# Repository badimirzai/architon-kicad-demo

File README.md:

# Architon KiCad BOM Demo

This repository is a minimal, reproducible demo of **Architon** scanning a **KiCad BOM CSV** and producing a deterministic JSON report.

What this demo proves (today):
- KiCad BOM CSV ingestion works
- A deterministic **DesignIR** JSON report is produced
- The workflow is automation-friendly (CI can run it)

What this demo does **not** claim (yet):
- Full schematic/netlist verification
- `rv scan .` project auto-discovery
- KiCad plugin integration

## Quickstart (local)

Prereqs:
- macOS / Linux
- Go installed (for `go install`), or install Architon via releases if you prefer

Install Architon CLI:

```bash
go install github.com/badimirzai/architon-cli@latest
```

Run scan:

```bash
rv scan bom/bom.csv --out .architon/architon-report.json
```

Inspect the report:

```bash
cat .architon/architon-report.json
```

## What’s in this repo

- `bom/bom.csv`  
  Exported from KiCad (Schematic Editor → Symbol Fields Table → Export CSV)

- `.architon/architon-report.json`  
  A reference report produced by running `rv scan` on the BOM

- `.github/workflows/architon.yml`  
  Runs `rv scan` on every push/PR

## Notes on “warnings”

If your BOM is missing optional/recommended fields (like Footprint for passives), Architon may emit parse warnings.
That’s fine for a demo, but if you want a “clean” demo output, assign footprints in KiCad before exporting the BOM.

## License

This demo repo is intended as an example project. Use any license you prefer for the repository itself.
Architon CLI is licensed separately in its own repository.

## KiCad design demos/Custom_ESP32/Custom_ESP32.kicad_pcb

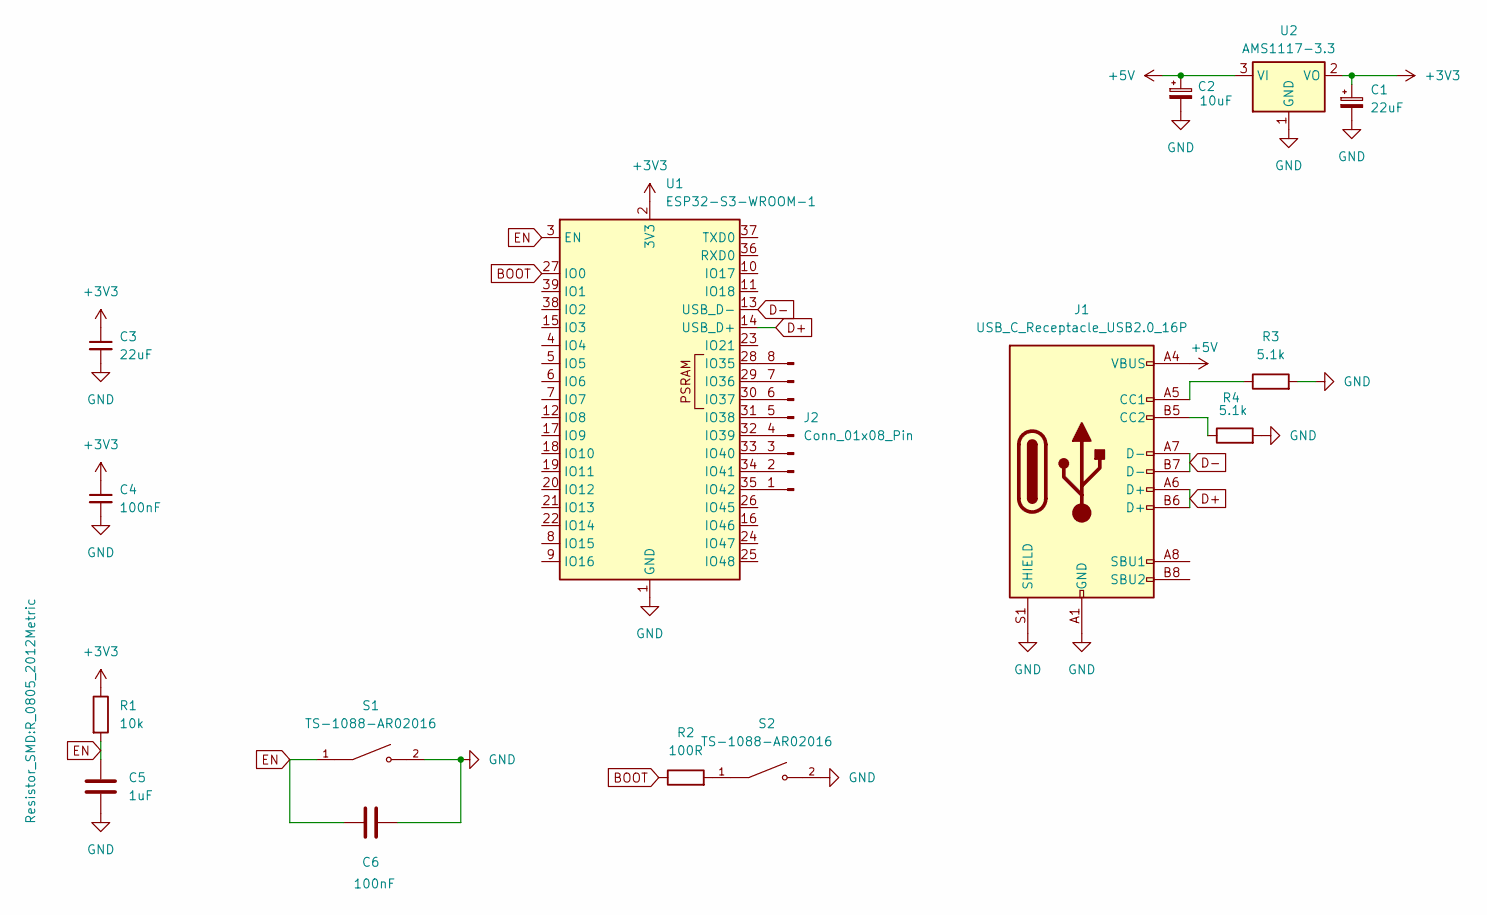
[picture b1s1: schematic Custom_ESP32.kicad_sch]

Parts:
C1: 22uF; CAPMP3216X180N
C2: 10uF; CAPMP3216X180N
C3: 22uF; 1uF_Unpolarized_CAPC2012X135N
C4, C6: 100nF; 1uF_Unpolarized_CAPC2012X135N
C5: 1uF; 1uF_Unpolarized_CAPC2012X135N
J1: USB_C_Receptacle_USB2.0_16P; GCT_USB4085-GF-A_REVA4
J2: Conn_01x08_Pin; PinHeader_1x08_P2.54mm_Vertical
R1: 10k; R_0805_2012Metric
R2: 100R; R_0805_2012Metric
R3, R4: 5.1k; R_0805_2012Metric
S1, S2: TS-1088-AR02016; SW_TS-1088-AR02016; PARTREV N/A
U1: ESP32-S3-WROOM-1
U2: AMS1117-3.3; SOT-223-3_TabPin2

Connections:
+3V3: C1.1, C3.1, C4.1, R1.1, U1.2 (3V3), U2.2 (VO)
+5V: C2.1, J1.A4 (VBUS), J1.A9 (VBUS), J1.B4 (VBUS), J1.B9 (VBUS), U2.3 (VI)
BOOT: R2.1, U1.27 (IO0)
D+: J1.A6 (D+), J1.B6 (D+), U1.14 (USB_D+)
D-: J1.A7 (D-), J1.B7 (D-), U1.13 (USB_D-)
EN: C5.1, C6.1, R1.2, S1.1, U1.3 (EN)
GND: C1.2, C2.2, C3.2, C4.2, C5.2, C6.2, J1.A1 (GND), J1.A12 (GND), J1.B1 (GND), J1.B12 (GND), J1.S1 (SHIELD), R3.2, R4.2, S1.2, S2.2, U1.1 (GND), U1.40 (GND), U1.41 (GND), U2.1 (GND)
unnamed: J1.A5 (CC1), R3.1
unnamed: J1.B5 (CC2), R4.1
unnamed: J2.1, U1.35 (IO42)
unnamed: J2.2, U1.34 (IO41)
unnamed: J2.3, U1.33 (IO40)
unnamed: J2.4, U1.32 (IO39)
unnamed: J2.5, U1.31 (IO38)
unnamed: J2.6, U1.30 (IO37)
unnamed: J2.7, U1.29 (IO36)
unnamed: J2.8, U1.28 (IO35)
unnamed: R2.2, S2.1

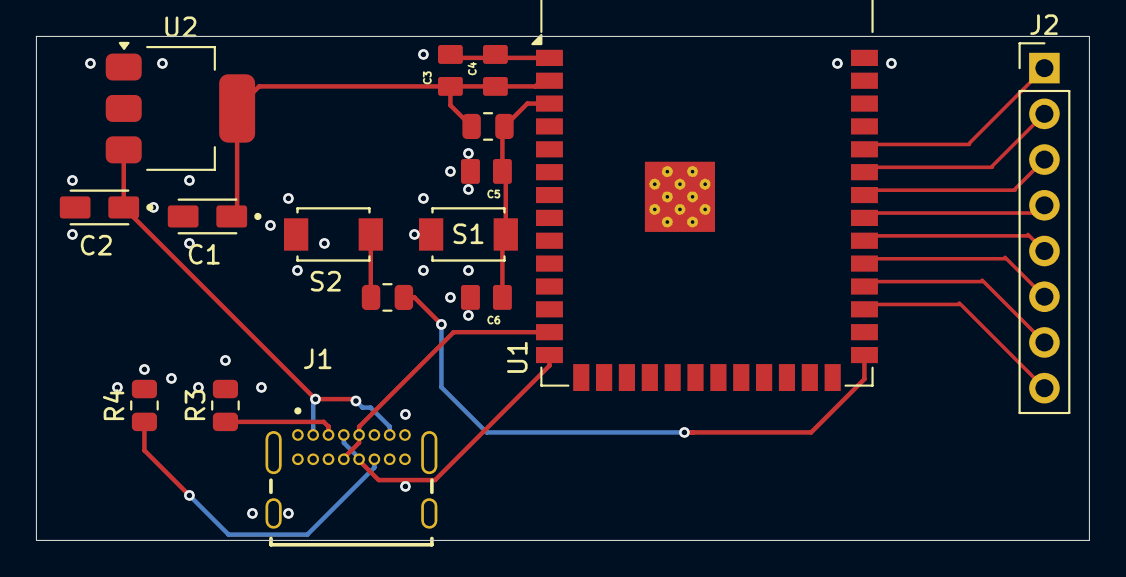
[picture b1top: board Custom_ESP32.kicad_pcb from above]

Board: 2 copper layers, 58.5 x 28.0 mm, 16 parts (0 on the bottom side), 18 nets.

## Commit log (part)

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2026-03-02 initial architon KiCad BOM demo
2026-03-02 update path of rv install
2026-03-02 add output directory got github actions
2026-03-23 added custom esp32 schematics/pcb project.
2026-04-28 feat: added kicad project files for overvoltage demo
2026-05-05 added test files/cases for kicad projects
2026-05-07 test: verify pullup resistor scenarios for architon kicad export
2026-05-07 docs: add remaining files for pull up resistor between
2026-05-07 docs: demo updated
2026-05-09 feat: first Studio iteration demo site
